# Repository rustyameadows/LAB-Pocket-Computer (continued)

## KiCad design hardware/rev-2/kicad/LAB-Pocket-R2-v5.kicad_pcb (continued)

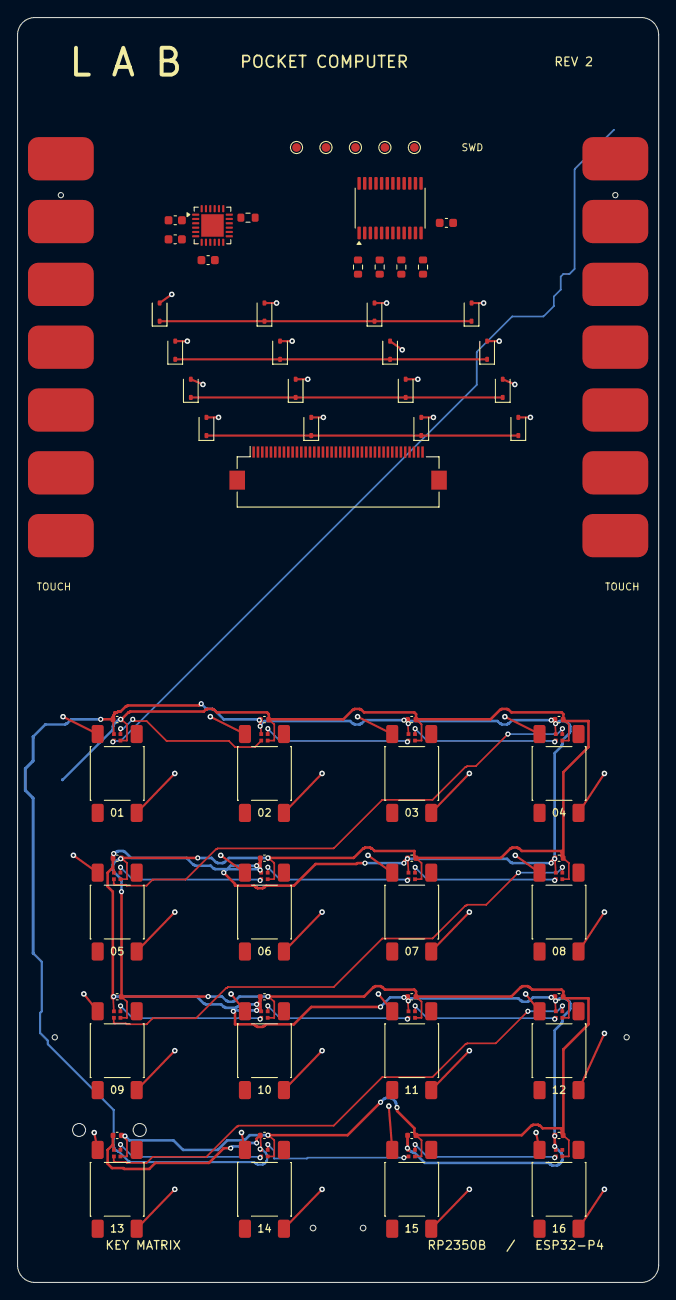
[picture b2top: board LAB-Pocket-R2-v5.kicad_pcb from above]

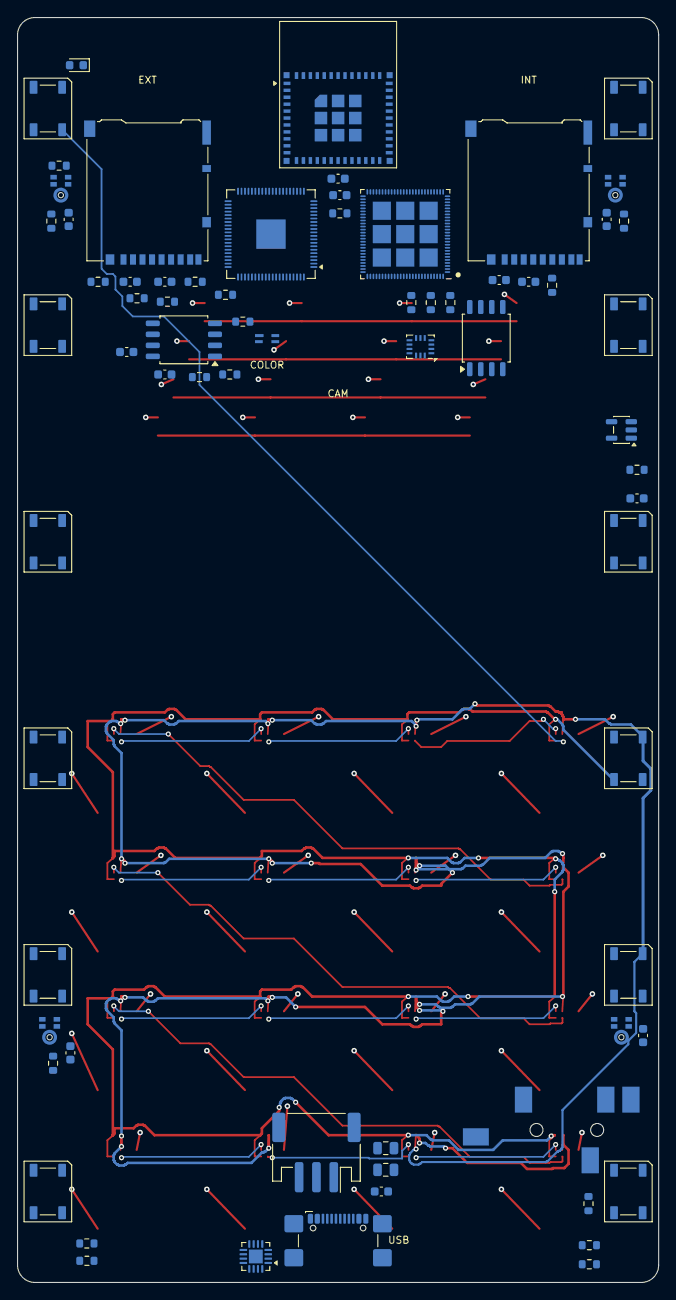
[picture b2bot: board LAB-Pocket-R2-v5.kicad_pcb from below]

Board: 4 copper layers, 74.0 x 146.0 mm, 165 parts (70 on the bottom side), 153 nets.

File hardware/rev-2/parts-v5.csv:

Refdes / assembly,Qty,Candidate MPN,Value / use,Land pattern / integration,Manufacturer document
C1 C3 C4 C5 C6 C7 C8 C9 C10 C11 C12 C14 C15 C17,14,C0603C104K5RACTU,100n,Capacitor_SMD:C_0603_1608Metric,datasheets/C0603C104K5RACTU.pdf
D1 D2 D3 D4 D5 D6 D7 D8 D9 D10 D11 D12 D13 D14 D15 D16,16,"BAS316,115",BAS316,Diode_SMD:D_SOD-323,datasheets/BAS316.pdf
R1 R2 R3 R4 R5 R21 R22 R23,8,CRCW060310K0FKEA,10k,Resistor_SMD:R_0603_1608Metric,datasheets/CRCW0603.pdf
SW1 SW2 SW3 SW4 SW5 SW6 SW7 SW8 SW9 SW10 SW11 SW12 SW13 SW14 SW15 SW16,16,TL3301NF160QG,TL3301,LAB:TL3301-key-v5,datasheets/TL3301NF160QG.pdf
U4,1,PCA9555PWR,PCA9555PWR,Package_SO:TSSOP-24_4.4x7.8mm_P0.65mm,datasheets/PCA9555PW.pdf
C2,1,C0603C222J5GACTU,2.2n C0G,Capacitor_SMD:C_0603_1608Metric,datasheets/C0603C222J5GACTU.pdf
U5,1,CY8CMBR3116-LQXI,CY8CMBR3116-LQXI,Package_DFN_QFN:QFN-24-1EP_4x4mm_P0.5mm_EP2.6x2.6mm,datasheets/CY8CMBR3116-LQXI.pdf
J2,1,FH12-40S-0.5SH(55),TTC273 • FH12-40S,Connector_FFC-FPC:Hirose_FH12-40S-0.5SH_1x40-1MP_P0.50mm_Horizontal,datasheets/FH12-40S-0.5SH.pdf
J3,1,DM3AT-SF-PEJM5,DM3AT • INT,Connector_Card:microSD_HC_Hirose_DM3AT-SF-PEJM5,datasheets/DM3AT-SF-PEJM5.pdf
J4,1,DM3AT-SF-PEJM5,DM3AT • EXT,Connector_Card:microSD_HC_Hirose_DM3AT-SF-PEJM5,datasheets/DM3AT-SF-PEJM5.pdf
R6 R7 R8 R9 R10 R11 R12 R13,8,CRCW060347K0FKEA,47k,Resistor_SMD:R_0603_1608Metric,datasheets/CRCW0603.pdf
C13,1,C0603C474K3RACTU,470n,Capacitor_SMD:C_0603_1608Metric,datasheets/C0603C474K3RACTU.pdf
D17,1,LTW-C191TS5,LTW-C191TS5,LED_SMD:LED_0603_1608Metric,datasheets/LTW-C191TS5.pdf
J5,1,SJ-43515TS-SMT-TR,SJ-43515TS-SMT,LAB:SJ-43515TS,datasheets/SJ-43514-SMT.pdf
LS1 LS2,2,AS01808AO-SC18-WP-R,PUI 8R / 1 W,off-board assembly,datasheets/AS01808AO-SC18-WP-R.pdf
MK1 MK2 MK3 MK4,4,IM70D122V01XTMA1,IM70D122V01,LAB:IM70D122,datasheets/IM70D122V01.pdf
R14 R15 R16 R17 R20,5,CRCW0603100RFKEA,100R,Resistor_SMD:R_0603_1608Metric,datasheets/CRCW0603.pdf
R18 R19,2,CRCW06034K70FKEA,4.7k,Resistor_SMD:R_0603_1608Metric,datasheets/CRCW0603.pdf
R28,1,CRCW0603150RFKEA,150R,Resistor_SMD:R_0603_1608Metric,datasheets/CRCW0603.pdf
U6,1,BMI270,BMI270,Package_LGA:Bosch_LGA-14_3x2.5mm_P0.5mm,datasheets/BMI270.pdf
U7,1,VEML3328,VEML3328,LAB:VEML3328,datasheets/VEML3328.pdf
LED1 LED2 LED3 LED4 LED5 LED6 LED7 LED8 LED9 LED10 LED11 LED12,12,WS2812B-V5/W,WS2812B-V5/W,LED_SMD:LED_WS2812B_PLCC4_5.0x5.0mm_P3.2mm,datasheets/WS2812B-V5-W.pdf
U8,1,SN74AHCT1G125DBVR,SN74AHCT1G125DBVR,Package_TO_SOT_SMD:SOT-23-5,datasheets/74AHCT1G125.pdf
C16 C18,2,C0603C105K8PACTU,1u,Capacitor_SMD:C_0603_1608Metric,datasheets/C0603C105K8PACTU.pdf
U1,1,ESP32-P4NRW32X,ESP32-P4NRW32X,LAB:ESP32-P4,datasheets/ESP32-P4.pdf
U3,1,ESP32-C6-MINI-1-N4,ESP32-C6-MINI-1-N4,RF_Module:ESP32-C6-MINI-1,datasheets/ESP32-C6-MINI-1.pdf
U9 U10,2,W25Q128JVSIQ,W25Q128JVSIQ,Package_SO:SOIC-8_5.3x5.3mm_P1.27mm,datasheets/W25Q128JV.pdf
U2,1,RP2350B,RP2350B,Package_DFN_QFN:QFN-80-1EP_10x10mm_P0.4mm_EP3.4x3.4mm,datasheets/RP2350B.pdf
BT1,1,LP735977JH+PCM+2 WIRES 70MM,LP735977JH,off-board assembly,datasheets/LP735977JH.pdf
C19 C20,2,C0805C475K8PACTU,4.7u,Capacitor_SMD:C_0805_2012Metric,datasheets/C0805C475K8PACTU.pdf
J1,1,USB4110-GF-A,USB-C USB 2.0 data and power,LAB:USB4110-v5,datasheets/USB4110-GF-A.pdf
J6,1,S3B-PH-SM4-TB,JST PH • keyed harness,Connector_JST:JST_PH_S3B-PH-SM4-TB_1x03-1MP_P2.00mm_Horizontal,datasheets/S3B-PH-SM4-TB.pdf
R24 R25,2,CRCW06035K10FKEA,5.1k,Resistor_SMD:R_0603_1608Metric,datasheets/CRCW0603.pdf
R26,1,CRCW06032K20FKEA,2.2k,Resistor_SMD:R_0603_1608Metric,datasheets/CRCW0603.pdf
R27,1,CRCW06033K00FKEA,3.0k,Resistor_SMD:R_0603_1608Metric,datasheets/CRCW0603.pdf
U11,1,BQ24074RGTR,BQ24074RGTR,Package_DFN_QFN:VQFN-16-1EP_3x3mm_P0.5mm_EP1.6x1.6mm,datasheets/BQ24074.pdf
LCD1,1,TTC273XSI-01,2.73 in RGB LCD,off-board assembly,datasheets/TTC273XSI-01.pdf
CAM1,1,114992267,IMX219-77 replacement camera,lens and flex; driver interface open,datasheets/IMX219-77-114992267.pdf
J6 mating,1,PHR-3,Mating 3-position housing,battery harness,datasheets/S3B-PH-SM4-TB.pdf
J6-1 J6-3,2,SPH-002T-P0.5S,"Wire contacts, final crimp and polarity to validate",two populated contacts; TS open,datasheets/S3B-PH-SM4-TB.pdf
CARD1,1,SDCS2/32GB,"32 GB microSD card, dimensional reference",internal removable media,datasheets/SDCS2-32GB.pdf
ADH1 ADH2,2,9495LE,Die-cut PET-carrier acrylic adhesive strip,20 × 55 × 0.17 mm each; candidate bond,datasheets/3M-9495LE.pdf
LED13 LED14 LED15 LED16 LED17 LED18 LED19 LED20 LED21 LED22 LED23 LED24 LED25 LED26 LED27 LED28,16,SK6805-EC10-000,Individually addressable key RGB,LAB:SK6805-EC10-v5,datasheets/SK6805-EC10-000.pdf
C21 C22 C23 C24 C25 C26 C27 C28 C29 C30 C31 C32 C33 C34 C35 C36,16,C0402C104K8RACTU,100 nF 10 V X7R key pixel bypass,Capacitor_SMD:C_0402_1005Metric,datasheets/C0402C104K8RACTU.pdf
